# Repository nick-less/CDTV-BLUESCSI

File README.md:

A Version of the CDTV SCSI Card with an added bluepill SCSI Emulator

Works with https://github.com/erichelgeson/BlueSCSI

```
Partlist

Part     Value          Package      Library      Position (mil)        Orientation

C1       100n           C025-024X044 rcl          (1318 3336)           R90
C2       100n           C025-024X044 rcl          (2406 2573)           R90
C3       47µ            E2,5-6E      rcl          (2144 3728)           R0
CN1      CDTV-EXPANSION CDTV-SLOT    Amiga        (1535 3964)           R180
D1       1N4148         DO35-7       diode        (2118 2309)           R0
F1       200mA          TE5          fuse         (1472 2144)           R180
IC1      74HC245N       DIL20        74xx-eu      (742 3468)            R180
IC2      WD33C93A       DIP40-6      Amiga        (1274 2824)           R180
JP1                     JP1          jumper       (160 2192)            R180
JP2                     JP1          jumper       (2868 814)            R270
JP3                     JP1          jumper       (528 1488)            R270
QG1      16Mhz          DIL14S       crystal      (2617 3349)           R90
R1       330            0207/7       rcl          (164 2475)            R270
R2       1k             0207/7       rcl          (164 2846)            R90
R3       1k             0207/7       rcl          (2827 2549)           R270
R4       1k             0207/7       rcl          (1712 2336)           R0
RN1      330            SIL10        resistor-sil (2338 2019)           R180
RN2      220            SIL10        resistor-sil (2238 2149)           R0
RN3      330            SIL10        resistor-sil (638 2019)            R0
RN4      220            SIL10        resistor-sil (738 2148)            R180
SD1      TF-HOLDER      TF-PULL      sd-mmc       (2688 272)            R180
SJ1                     SJ_2         jumper       (1697 3367)           R0
U$1                     BLUE_PILL    BluePill     (864 992)             R90
X1       057-050-1      057-050-1    con-panduit  (1488 1746)           R0
X2                      F25H         SparkFun     (1152 304)            R180
```

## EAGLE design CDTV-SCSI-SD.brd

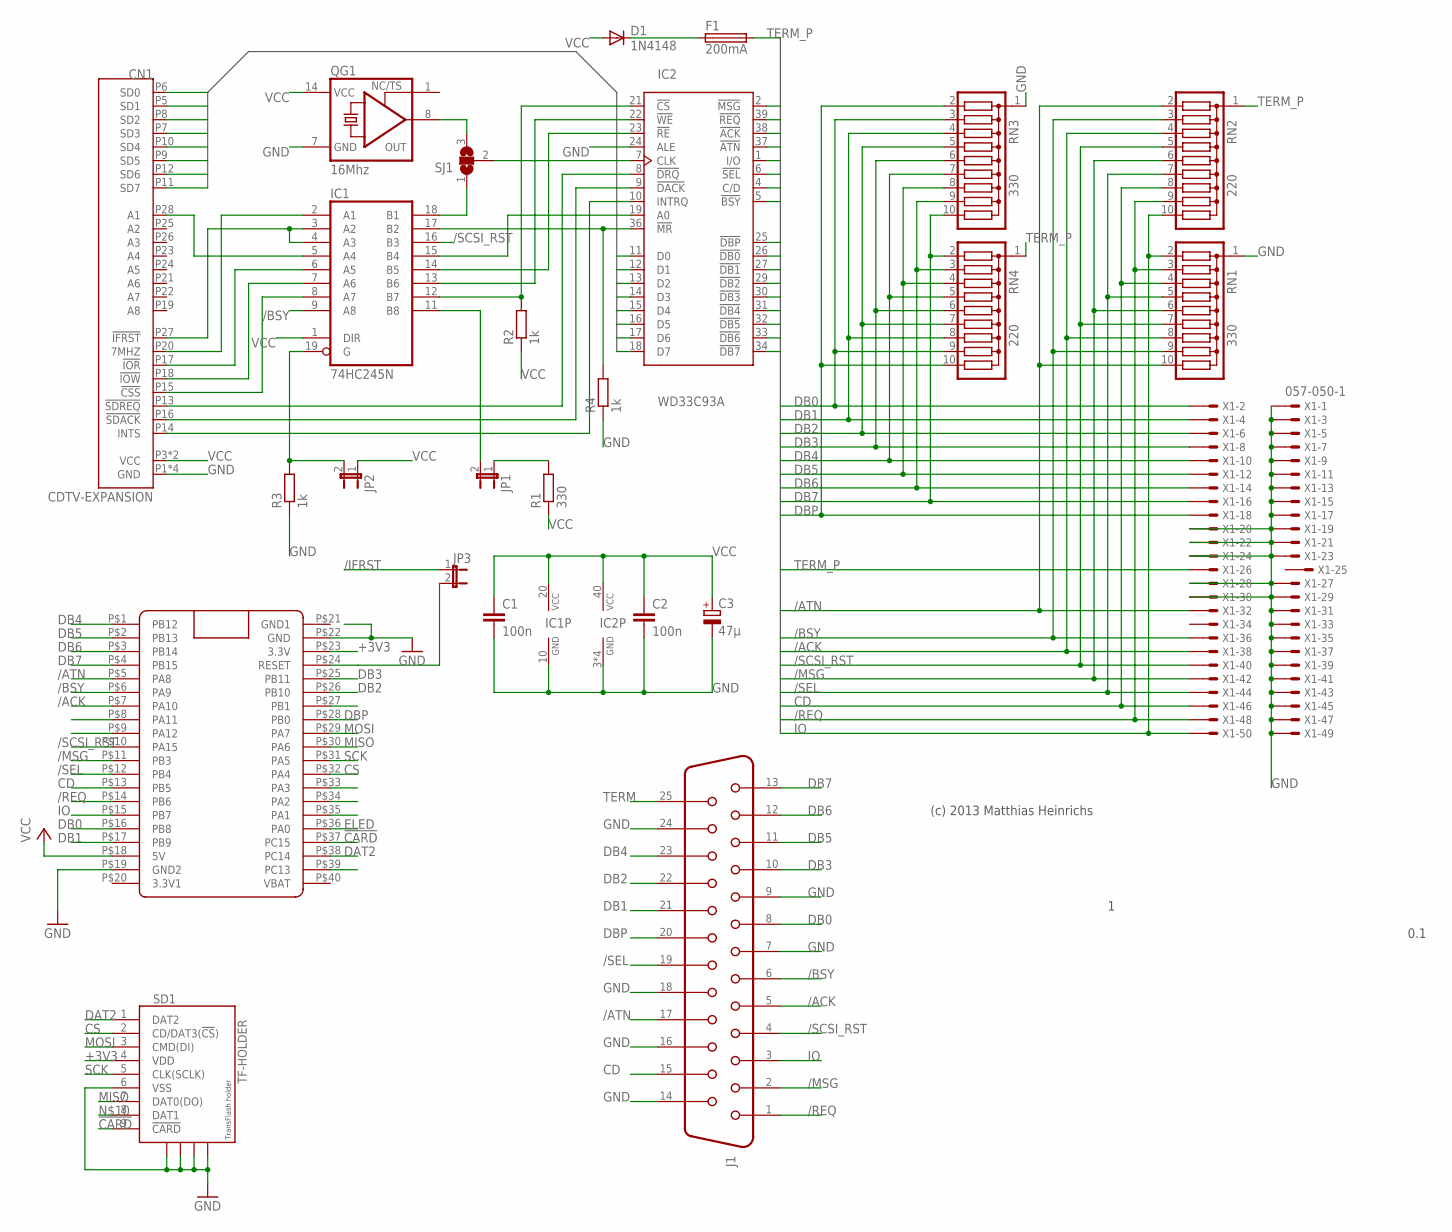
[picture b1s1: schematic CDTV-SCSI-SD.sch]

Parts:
C1, C2: 100n; C025-024X044
C3: 47µ; E2,5-6E
CN1: CDTV-EXPANSION; CDTV-SLOT
D1: 1N4148; DO35-7
F1: 200mA; TE5
IC1: 74HC245N; DIL20
IC2: WD33C93A; DIP40-6
J1: 61802529321
JP1, JP2, JP3: JP1E; JP1
QG1: 16Mhz; DIL14S
R1: 330; 0207/7
R2, R3, R4: 1k; 0207/7
RN1, RN3: 330; SIL10
RN2, RN4: 220; SIL10
SD1: TF-HOLDER; TF-PULL
SJ1: SJ2W; SJ_2
U$1: BLUE_PILL
X1: 057-050-1

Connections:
7MHZ: CN1.P20 (7MHZ), IC1.2 (A1)
!CARD: SD1.9 (!CARD), U$1.P$37 (PC15)
+3V3: SD1.4 (VDD), U$1.P$23 (3.3V)
/ACK: IC2.38 (!ACK), J1.5, RN1.8, RN2.4, U$1.P$7 (PA10), X1.38
/ATN: IC2.37 (!ATN), J1.17, RN1.10, RN2.2, U$1.P$5 (PA8), X1.32
/BSY: IC1.9 (A8), IC2.5 (!BSY), J1.6, RN1.9, RN2.3, U$1.P$6 (PA9), X1.36
/BSY_B: IC1.11 (B8), JP1.2
/CS: IC1.12 (B7), IC2.21 (!CS), R2.2
/CSS: CN1.P15 (!CSS), IC1.8 (A7)
/ENABLE: IC1.19 (G), JP2.2, R3.2
/IFRST: CN1.P27 (!IFRST), IC1.3 (A2), IC1.4 (A3), JP3.1
/INTS: CN1.P14 (INTS), IC2.10 (INTRQ)
/IOR: CN1.P17 (!IOR), IC1.6 (A5)
/IOW: CN1.P18 (!IOW), IC1.7 (A6)
/MR: IC1.17 (B2), IC2.36 (!MR), R4.2
/MSG: IC2.2 (!MSG), J1.2, RN1.6, RN2.6, U$1.P$11 (PB3), X1.42
/RE: IC1.14 (B5), IC2.23 (!RE)
/REQ: IC2.39 (!REQ), J1.1, RN1.3, RN2.9, U$1.P$14 (PB6), X1.48
/SCSI_RST: IC1.16 (B3), J1.4, RN1.7, RN2.5, U$1.P$10 (PA15), X1.40
/SDACK: CN1.P16 (!SDACK), IC2.9 (!DACK)
/SDREQ: CN1.P13 (!SDREQ), IC2.8 (!DRQ)
/SEL: IC2.6 (!SEL), J1.19, RN1.5, RN2.7, U$1.P$12 (PB4), X1.44
/WE: IC1.13 (B6), IC2.22 (!WE)
A1: CN1.P28 (A1), IC1.5 (A4)
B_A1: IC1.15 (B4), IC2.19 (A0)
CD: IC2.4 (C/D), J1.15, RN1.4, RN2.8, U$1.P$13 (PB5), X1.46
CLK: IC2.7 (CLK), SJ1.2
CLK_7: IC1.18 (B1), SJ1.1
CLK_16M: QG1.8 (OUT), SJ1.3
CS: SD1.2 (CD/DAT3(!CS!)), U$1.P$32 (PA4)
DAT2: SD1.1 (DAT2), U$1.P$38 (PC14)
DB0: IC2.26 (!DB0), J1.8, RN3.3, RN4.9, U$1.P$16 (PB8), X1.2
DB1: IC2.27 (!DB1), J1.21, RN3.4, RN4.8, U$1.P$17 (PB9), X1.4
DB2: IC2.29 (!DB2), J1.22, RN3.5, RN4.7, U$1.P$26 (PB10), X1.6
DB3: IC2.30 (!DB3), J1.10, RN3.6, RN4.6, U$1.P$25 (PB11), X1.8
DB4: IC2.31 (!DB4), J1.23, RN3.7, RN4.5, U$1.P$1 (PB12), X1.10
DB5: IC2.32 (!DB5), J1.11, RN3.8, RN4.4, U$1.P$2 (PB13), X1.12
DB6: IC2.33 (!DB6), J1.12, RN3.9, RN4.3, U$1.P$3 (PB14), X1.14
DB7: IC2.34 (!DB7), J1.13, RN3.10, RN4.2, U$1.P$4 (PB15), X1.16
DBP: IC2.25 (!DBP), J1.20, RN3.2, RN4.10, U$1.P$28 (PB0), X1.18
ELED: U$1.P$36 (PA0)
GND: C1.2, C2.2, C3.-, CN1.P1 (GND), CN1.P2 (GND), CN1.P29 (GND), CN1.P30 (GND), IC1.10 (GND), IC2.3 (GND1), IC2.20 (GND1), IC2.24 (ALE), IC2.28 (GND1), IC2.35 (GND1), J1.7, J1.9, J1.14, J1.16, J1.18, J1.24, QG1.7 (GND), R3.1, R4.1, RN1.1, RN3.1, SD1.6 (VSS), SD1.S1, SD1.S2, SD1.S3, SD1.S4, U$1.P$19 (GND2), U$1.P$22 (GND), X1.1, X1.3, X1.5, X1.7, X1.9, X1.11, X1.13, X1.15, X1.17, X1.19, X1.20, X1.21, X1.22, X1.23, X1.24, X1.27, X1.28, X1.29, X1.30, X1.31, X1.33, X1.35, X1.37, X1.39, X1.41, X1.43, X1.45, X1.47, X1.49
GND1: U$1.P$21 (GND1)
IO: IC2.1 (I/O), J1.3, RN1.2, RN2.10, U$1.P$15 (PB7), X1.50
LED_POW: JP1.1, R1.2
MISO: SD1.7 (DAT0(DO)), U$1.P$30 (PA6)
MOSI: SD1.3 (CMD(DI)), U$1.P$29 (PA7)
unnamed: JP3.2, U$1.P$24 (RESET)
SCK: SD1.5 (CLK(SCLK)), U$1.P$31 (PA5)
SD0: CN1.P6 (SD0), IC2.11 (D0)
SD1: CN1.P5 (SD1), IC2.12 (D1)
SD2: CN1.P8 (SD2), IC2.13 (D2)
SD3: CN1.P7 (SD3), IC2.14 (D3)
SD4: CN1.P10 (SD4), IC2.15 (D4)
SD5: CN1.P9 (SD5), IC2.16 (D5)
SD6: CN1.P12 (SD6), IC2.17 (D6)
SD7: CN1.P11 (SD7), IC2.18 (D7)
TERM: J1.25
TERM_P: F1.2, RN2.1, RN4.1, X1.26
TP_UNFUSED: D1.C, F1.1
VCC: C1.1, C2.1, C3.+, CN1.P3 (VCC), CN1.P4 (VCC), D1.A, IC1.1 (DIR), IC1.20 (VCC), IC2.40 (VCC1), JP2.1, QG1.14 (VCC), R1.1, R2.1, U$1.P$18 (5V)

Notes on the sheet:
0.1
(c) 2013 Matthias Heinrichs

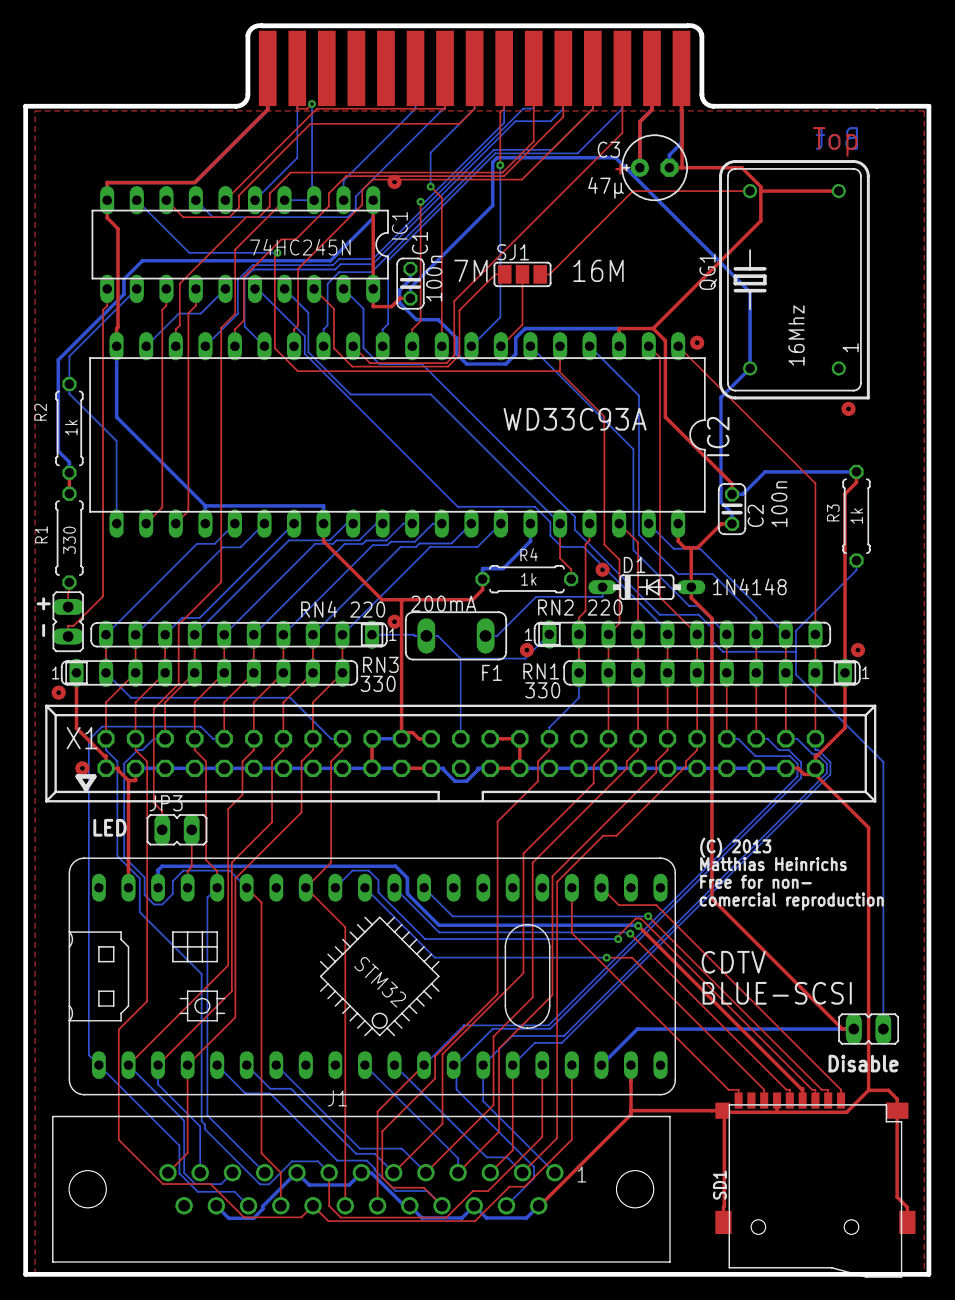
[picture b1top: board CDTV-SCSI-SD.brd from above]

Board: 2 copper layers, 77.6 x 107.3 mm, 25 parts (0 on the bottom side), 58 nets.

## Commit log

2022-04-28 add gitignore
2022-04-28 removed lock files
2022-05-08 add pdf, add png
2022-05-13 (fix), db25 was male instead of female
2022-05-13 (fix), removed broken image
2022-05-15 (fix), MOSI and SCK were switched
2022-05-16 (enhancement), add picture of board
2022-05-16 (enhancement), update pdf
2022-08-07 added a backpanel model
2022-08-07 updated backpanel model
2025-06-20 fix(doc): add complete build image

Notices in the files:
parts and their libraries:
InputOutputIO: Copyright: Würth Elektronik
